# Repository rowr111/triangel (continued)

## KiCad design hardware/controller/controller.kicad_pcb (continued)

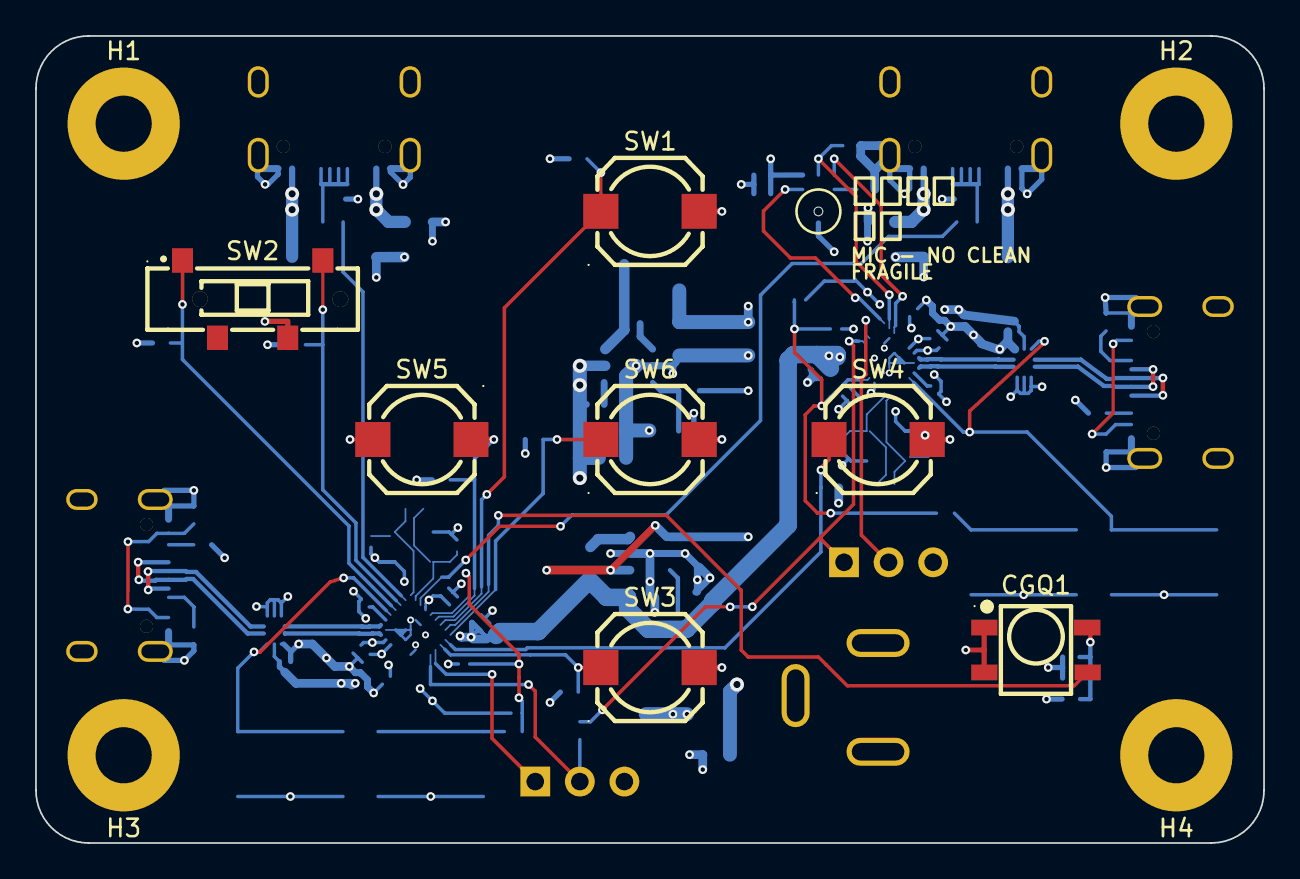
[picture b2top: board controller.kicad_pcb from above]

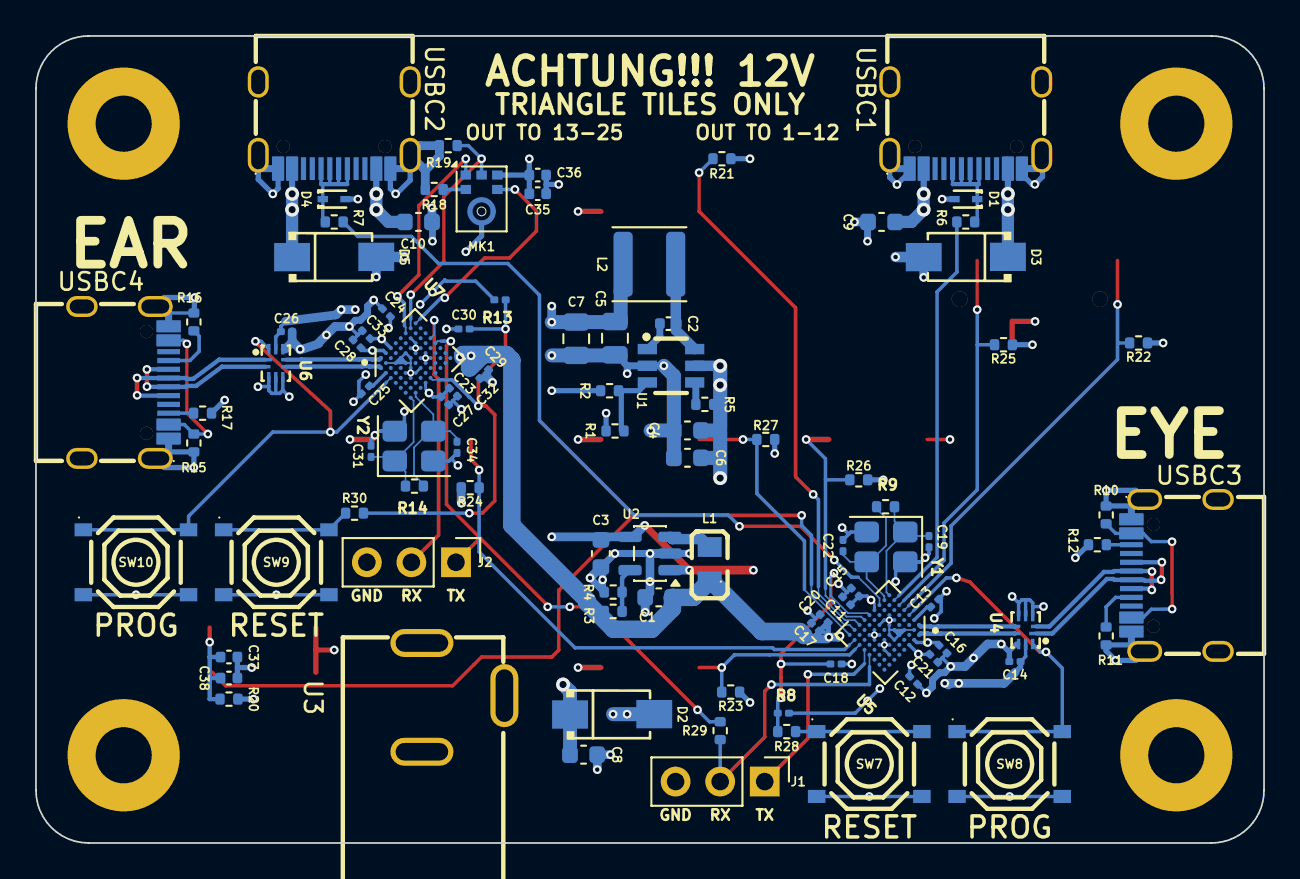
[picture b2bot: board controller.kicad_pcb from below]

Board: 4 copper layers, 70.0 x 46.0 mm, 106 parts (95 on the bottom side), 57 nets.

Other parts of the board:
J2: Conn_01x03; PinHeader_1x03_P2.54mm_Vertical
R30: 100Ω; R_0402_1005Metric
SW9, SW10: TS-1187A-B-A-B; SW-SMD_4P-L5.1-W5.1-P3.70-LS6.5-TL_H1.5

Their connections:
/Ear/EAR_RX: J2.2; also elsewhere on the board
AUDIO_LINK: J2.1; also elsewhere on the board
GND: J2.3, SW9.3, SW9.4, SW10.3, SW10.4; also elsewhere on the board
unnamed: R30.1, SW9.1, SW9.2
unnamed 36: SW10.1, SW10.2; also elsewhere on the board
unnamed 48: R30.2; also elsewhere on the board

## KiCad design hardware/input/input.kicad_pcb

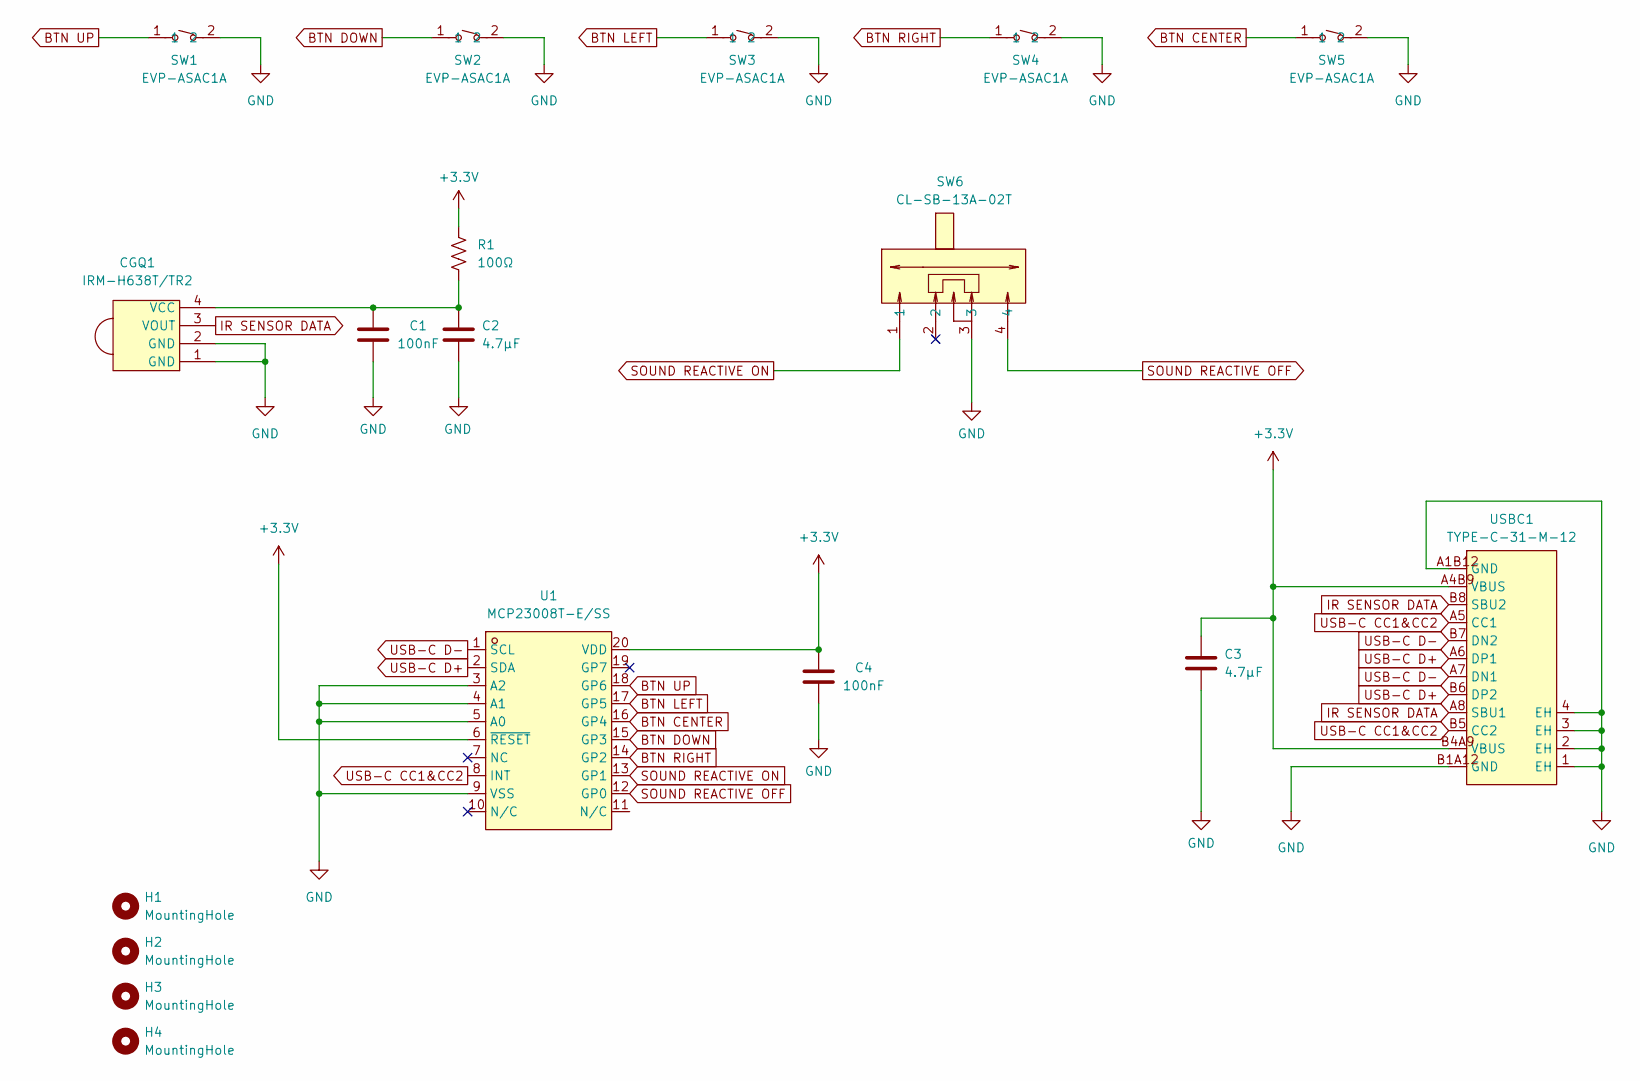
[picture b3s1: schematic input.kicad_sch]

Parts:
C1, C4: 100nF; C_0402_1005Metric; LCSC Part # C1525
C2, C3: 4.7µF; C_0603_1608Metric; LCSC Part # C19666
CGQ1: IRM-H638T/TR2; SENSOR-SMD_IRM-H638T-TR2-TL; MPN IRM-H638T/TR2; LCSC Part # C91447
H1, H2, H3, H4: MountingHole; MountingHole_3.2mm_M3_Pad
R1: 100Ω; R_0603_1608Metric; LCSC Part # C22775
SW1, SW2, SW3, SW4, SW5: EVP-ASAC1A; SW-SMD_PANASONIC_EVPASXXX; MPN EVP-ASAC1A; LCSC Part # C4365033
SW6: CL-SB-13A-02T; SW-SMD_CL-SB-13A-0X; MPN CL-SB-13A-02T; LCSC Part # C2921655
U1: MCP23008T-E/SS; SSOP-20_L7.2-W5.3-P0.65-LS7.8-TL; MPN MCP23008T-E/SS; LCSC Part C629435
USBC1: TYPE-C-31-M-12; USB-C_SMD-TYPE-C-31-M-12_1; MPN TYPE-C-31-M-12; LCSC Part C165948

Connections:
+3.3V: C3.2, C4.1, R1.2, U1.6 (~RESET), U1.20 (VDD), USBC1.A4B9 (VBUS), USBC1.B4A9 (VBUS)
BTN CENTER: SW5.1, U1.16 (GP4)
BTN DOWN: SW2.1, U1.15 (GP3)
BTN LEFT: SW3.1, U1.17 (GP5)
BTN RIGHT: SW4.1, U1.14 (GP2)
BTN UP: SW1.1, U1.18 (GP6)
GND: C1.2, C2.1, C3.1, C4.2, CGQ1.1 (GND), CGQ1.2 (GND), SW1.2, SW2.2, SW3.2, SW4.2, SW5.2, SW6.3, U1.3 (A2), U1.4 (A1), U1.5 (A0), U1.9 (VSS), USBC1.1 (EH), USBC1.2 (EH), USBC1.3 (EH), USBC1.4 (EH), USBC1.A1B12 (GND), USBC1.B1A12 (GND)
IR SENSOR DATA: CGQ1.3 (VOUT), USBC1.A8 (SBU1), USBC1.B8 (SBU2)
unnamed: C1.1, C2.2, CGQ1.4 (VCC), R1.1
SOUND REACTIVE OFF: SW6.4, U1.12 (GP0)
SOUND REACTIVE ON: SW6.1, U1.13 (GP1)
USB-C CC1&CC2: U1.8 (INT), USBC1.A5 (CC1), USBC1.B5 (CC2)
USB-C D+: U1.2 (SDA), USBC1.A6 (DP1), USBC1.B6 (DP2)
USB-C D-: U1.1 (SCL), USBC1.A7 (DN1), USBC1.B7 (DN2)

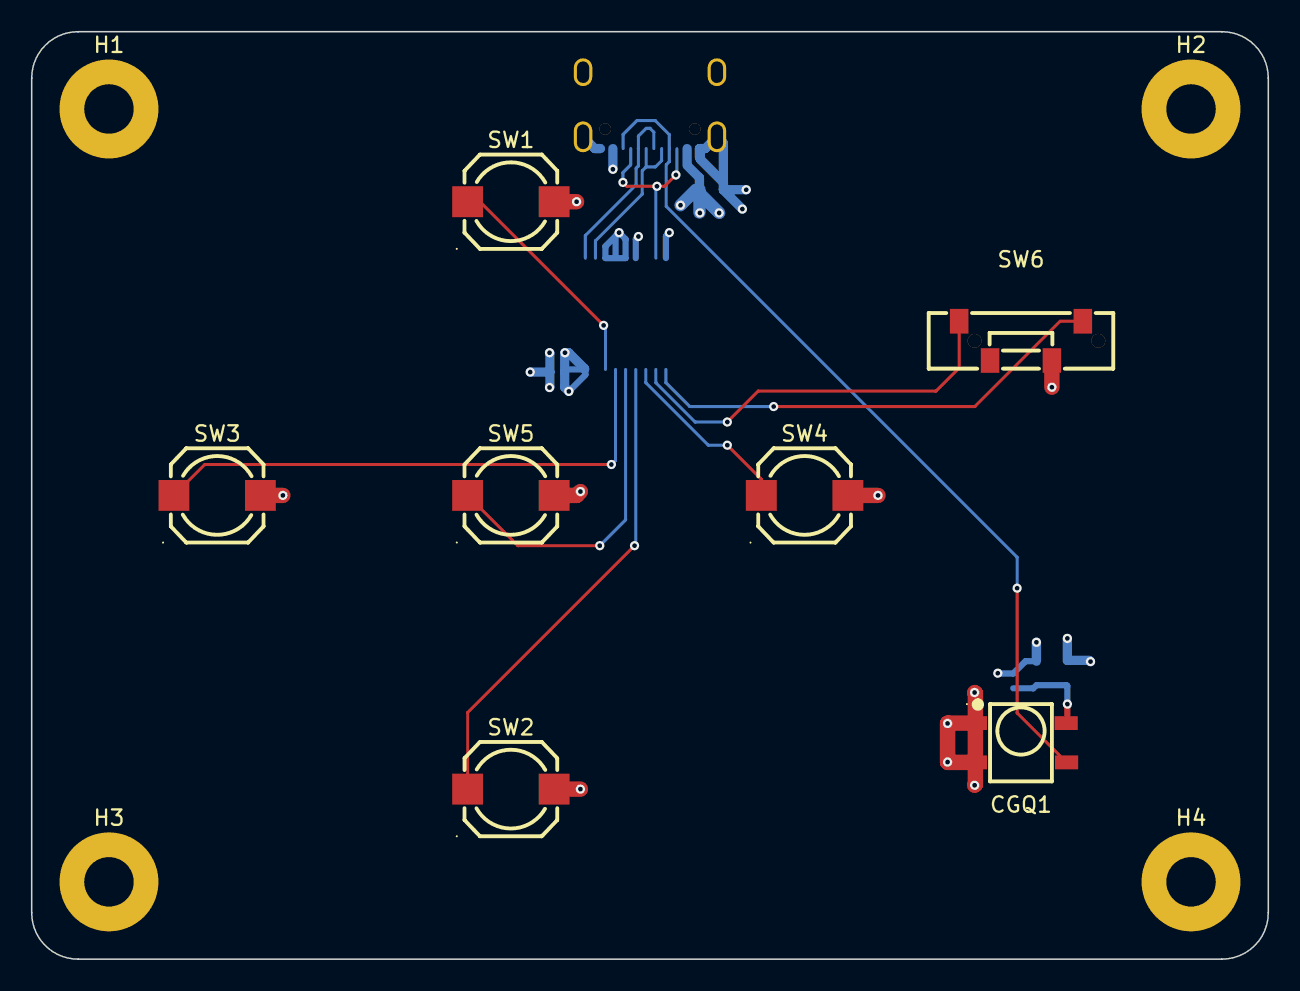
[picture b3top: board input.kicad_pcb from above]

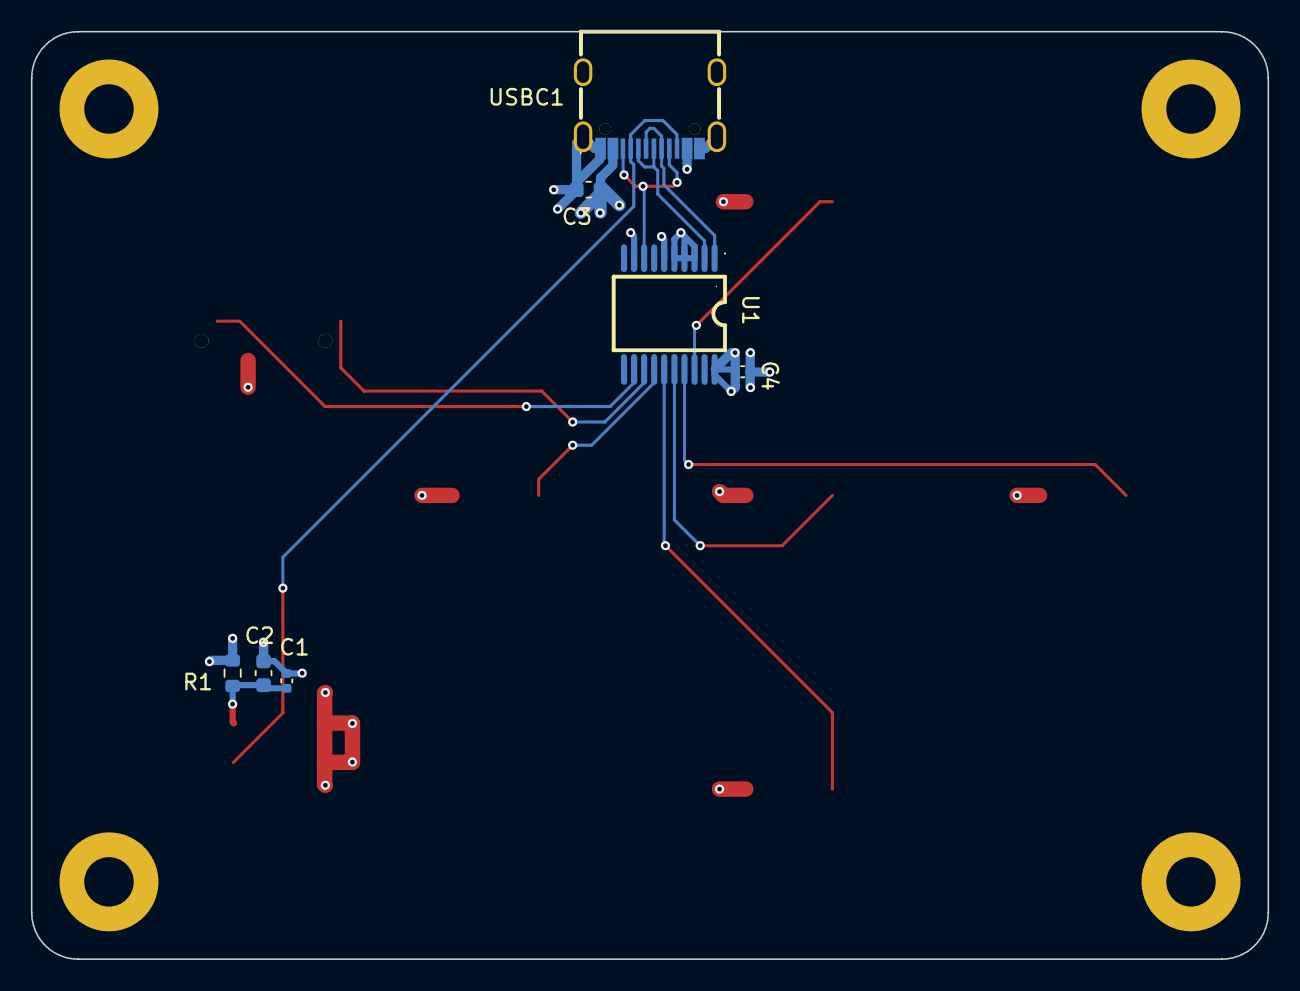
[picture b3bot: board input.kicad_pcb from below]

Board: 4 copper layers, 80.0 x 60.0 mm, 18 parts (7 on the bottom side), 14 nets.

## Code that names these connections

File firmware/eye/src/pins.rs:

use bao1x_api::iox::IoxHal;
use bao1x_api::{IoSetup, IoxDir, IoxEnable, IoxFunction, IoxPort};

// LED output
// BIO pin 4 = PB4 -> chain 1 (288 LEDs, enters at board 1)   [schematic: LED DATA_1, U2.7]
// BIO pin 5 = PB5 -> chain 2 (312 LEDs, enters at board 13)  [schematic: LED DATA_2, U2.6]
// The v3 all-in-one controller uses BIO pin 26 = PC10 for chain 1 and BIO pin 25 = PC9 for chain 2.
#[cfg(all(not(feature = "previewer"), not(feature = "combined-board")))]
pub const LED_BIO_PIN: u8 = 4;
#[cfg(all(not(feature = "previewer"), not(feature = "combined-board")))]
pub const LED_BIO_PIN_2: u8 = 5;
#[cfg(all(not(feature = "previewer"), feature = "combined-board"))]
pub const LED_BIO_PIN: u8 = 26;
#[cfg(all(not(feature = "previewer"), feature = "combined-board"))]
pub const LED_BIO_PIN_2: u8 = 25;

// Audio UART from the ear: UART2 RX. The eye's own TX (PB14) is not used.
pub const AUDIO_UART_RX_PORT: IoxPort = IoxPort::PB;
pub const AUDIO_UART_RX_PIN: u8 = 13;

// D-pad and 3-position sound switch. They sit behind an I2C expander on the separate input
// board; with the `combined-board` feature they are wired to eye GPIOs. The IR sensor is
// on PC8, or PC3 on the v3 all-in-one controller.

#[cfg(feature = "combined-board")]
pub use combined_board::*;

#[cfg(feature = "combined-board")]
mod combined_board {
    use super::IoxPort;

    // D-pad buttons, active-low with external pull-ups.
    pub const BTN_UP_PORT: IoxPort = IoxPort::PC;
    pub const BTN_UP_PIN: u8 = 7;
    pub const BTN_DOWN_PORT: IoxPort = IoxPort::PC;
    pub const BTN_DOWN_PIN: u8 = 0;
    pub const BTN_LEFT_PORT: IoxPort = IoxPort::PC;
    pub const BTN_LEFT_PIN: u8 = 8;
    pub const BTN_RIGHT_PORT: IoxPort = IoxPort::PC;
    pub const BTN_RIGHT_PIN: u8 = 1;
    pub const BTN_CENTER_PORT: IoxPort = IoxPort::PC;
    pub const BTN_CENTER_PIN: u8 = 2;

    // 3-position sound switch. Its common is tied to +3.3V and each throw has a 10k pull-down,
    // so the selected line reads HIGH and the center position reads both LOW. On the v3
    // schematic they are SOUND REACTIVE ON and SOUND REACTIVE OFF.
    pub const SW_ON_PORT: IoxPort = IoxPort::PC;
    pub const SW_ON_PIN: u8 = 12;
    pub const SW_OFF_PORT: IoxPort = IoxPort::PC;
    pub const SW_OFF_PIN: u8 = 11;
}

#[cfg(not(feature = "combined-board"))]
pub use input_board::*;

#[cfg(not(feature = "combined-board"))]
mod input_board {
    use super::IoxPort;

    // MCP23008 I2C expander carrying the d-pad and the sound switch. A0/A1/A2 are tied to
    // GND, giving 7-bit address 0x20. Every input is active-low on its internal pull-ups.
    pub const EXPANDER_ADDR: u8 = 0x20;

    // The expander bit of each input. Bit 7 is spare.
    pub const EXP_BIT_SW_OFF: u8 = 0;
    pub const EXP_BIT_SW_ON: u8 = 1;
    pub const EXP_BIT_RIGHT: u8 = 2;
    pub const EXP_BIT_DOWN: u8 = 3;
    pub const EXP_BIT_CENTER: u8 = 4;
    pub const EXP_BIT_LEFT: u8 = 5;
    pub const EXP_BIT_UP: u8 = 6;

    // Expander interrupt line: open-drain and active-low, pulled up at the eye. It asserts
    // when an input changes.
    pub const EXPANDER_INT_PORT: IoxPort = IoxPort::PC;
    pub const EXPANDER_INT_PIN: u8 = 7;
}

// IR receiver (Everlight IRM-H638T/TR2): idle HIGH, burst LOW. It is on PC8 (socket U1.7),
// which is BIO bit 24: PB0-15 are BIO 0-15 and PC0-15 are BIO 16-31. The v3 all-in-one
// controller has it on PC3, BIO bit 19.
#[cfg(not(feature = "combined-board"))]
pub const IR_BIO_PIN: u8 = 24;
#[cfg(feature = "combined-board")]
pub const IR_BIO_PIN: u8 = 19;

/// Configure a pin as a schmitt-trigger input for `function`. Turn `pull_up` off on lines
/// with external pull-downs, so the two do not form a voltage divider.
pub fn setup_input_pin(
    iox: &IoxHal,
    port: IoxPort,
    pin: u8,
    function: IoxFunction,
    pull_up: IoxEnable,
) {
    iox.setup_pin(
        port,
        pin,
        Some(IoxDir::Input),
        Some(function),
        Some(IoxEnable::Enable), // schmitt trigger
        Some(pull_up),
        None,
        None,
    );
}

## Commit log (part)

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2026-05-28 make exclusion zones around mounting holes circles
2026-05-28 simple audio pattern for testing
2026-05-28 remove some unused code and set pins
2026-05-28 make audio pattern have one solid led
2026-05-28 make the serial port auto-reconnect for the previewer
2026-05-29 some progress
2026-05-29 fixes
2026-05-29 hacktacular but at least it outputs audio level that looks like something
2026-05-30 buttons code and turn off sound reactivity debugging default
2026-05-30 some reformatting/cleanup and ir stuff
2026-05-30 add cap to triangle board and start controller board
2026-05-30 use different socket for data vs power to avoid accidents
2026-05-30 remove unnecessary test pad and add silkscreen for sockets
2026-05-31 remove wrong part from controller board
2026-05-31 holes only.
2026-06-02 updating components on triangle board - in progress
2026-06-04 trying and failing to fix the usb-c
2026-06-05 redraw fill zone
2026-06-06 add more power items
2026-06-07 fixing schematic
2026-06-07 trying to fix schematic
2026-06-07 adjust placement
2026-06-07 more placement adjustment
2026-06-07 more moving things around
2026-06-07 add another capacitor
2026-06-07 split the leds into two for sending through two daisy chains
2026-06-07 fix labels
2026-06-08 remove old usb from controller
2026-06-08 placing more components for controller board
2026-06-10 more controller board work, consolidation/revision of design
2026-06-10 schematic renaming
2026-06-11 more controller board work
2026-06-14 adding labels and the barrel connector
2026-06-14 hook up all the dabao headers and one more voltage converter
2026-06-15 re-order the numbers on the schematic for tidiness
2026-06-15 renaming parts for consistency
2026-06-15 fix part numbering
2026-06-15 copy footprints
2026-06-15 making initial pcb file and importing items
2026-06-15 more footprint updating
2026-06-15 updating symbols and board
2026-06-15 moving some more things around
2026-06-17 rotate/move around items on controller board
2026-06-18 adding some more stuff
2026-06-18 controller layout work
2026-06-19 placement and initial routing
2026-06-19 update fill
2026-06-20 rearrange the pins a bit and less insane routing
2026-06-21 controller layout updates
2026-06-21 updating firmware to reflect pin assignments
2026-06-22 fix: reset pattern cycle timer on manual next/prev
2026-06-22 fix: clear audio activity flag when ear stops sending
2026-06-22 naptime
2026-06-22 fix: retry audio UART init instead of dying on first failure
2026-06-22 fix: guard HorizontalScan against zero period_ms
2026-06-22 eye: give each setlist its own cursor
2026-06-22 eye: interrupt-driven UART RX for audio
2026-06-29 add buttons to the previewer and have the eye respond to their data over serial
2026-06-29 transitions and restructure patterns folder
